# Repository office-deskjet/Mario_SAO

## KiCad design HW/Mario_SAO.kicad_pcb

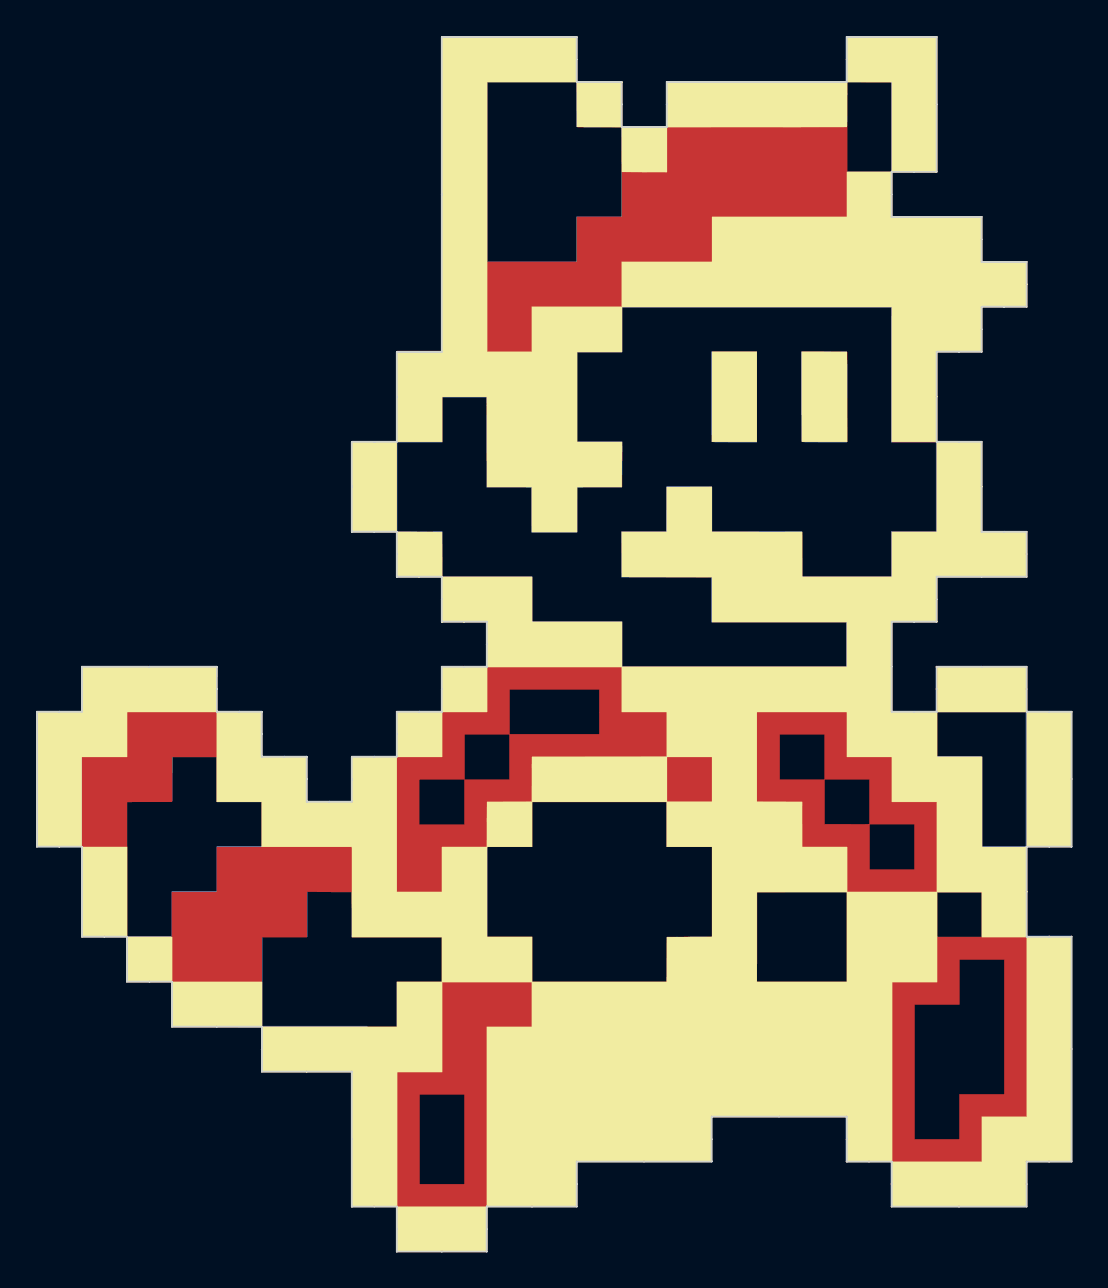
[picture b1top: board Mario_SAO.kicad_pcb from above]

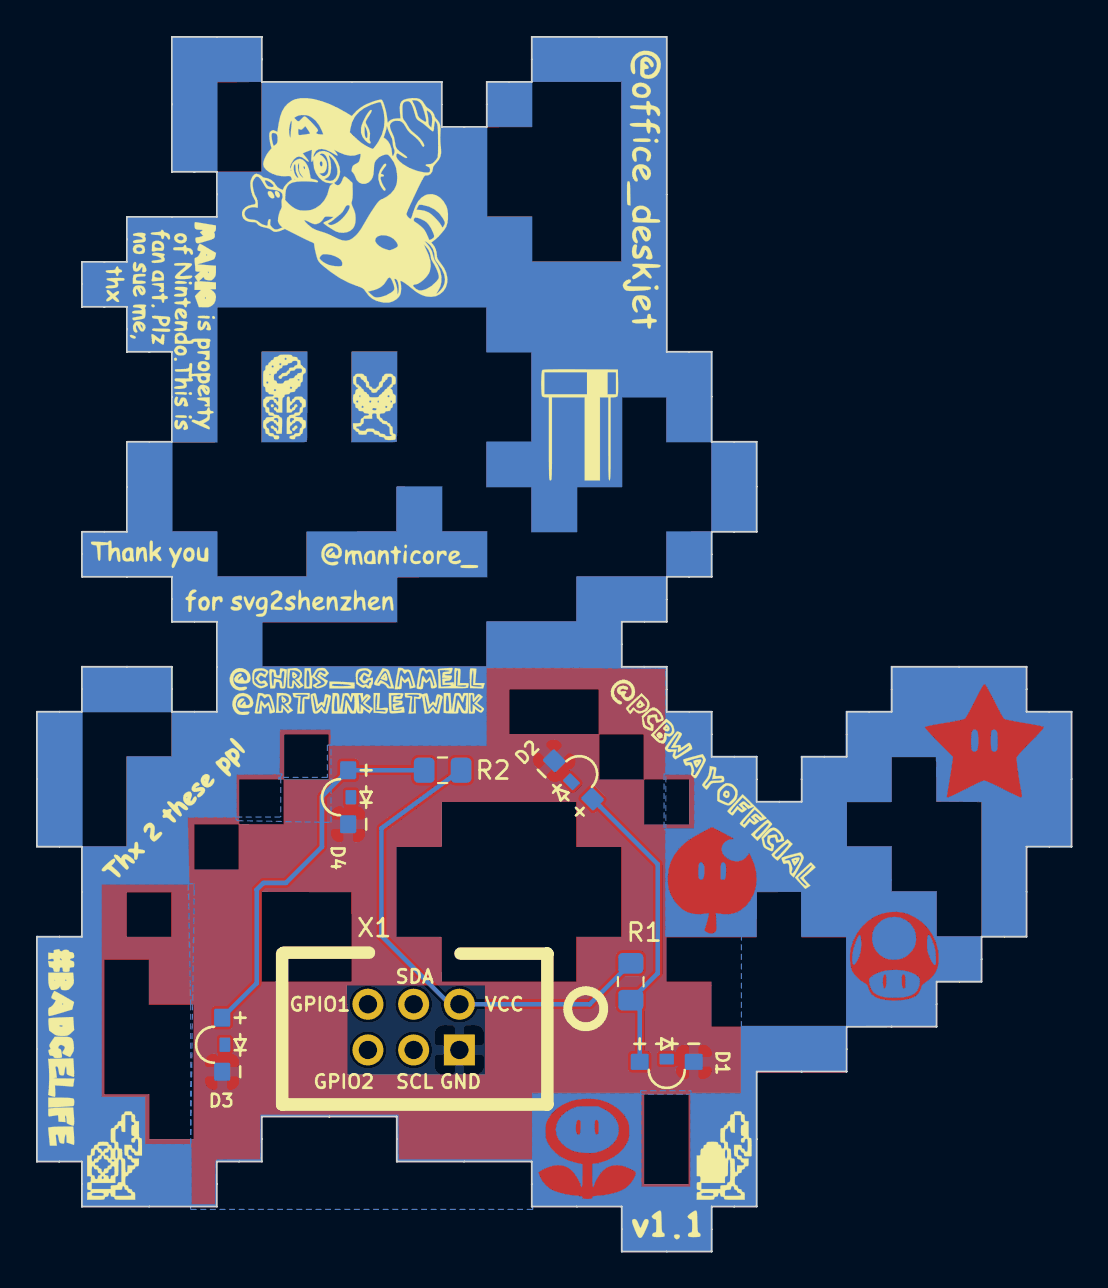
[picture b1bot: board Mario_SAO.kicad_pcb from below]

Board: 2 copper layers, 57.5 x 67.5 mm, 7 parts (6 on the bottom side), 4 nets.

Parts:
D1, D2, D3, D4: LED; 1204_SIDE_VIEW_LED
R1, R2: 50R; R_0805_2012Metric_Pad1.15x1.40mm_HandSolder
X1: Badgelife_sao_connector_v169bis; Badgelife-SAOv169-SAO-2x3

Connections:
GND: D1.1, D2.1, D3.1, D4.1, X1.2
unnamed: D1.2, D2.2, R1.2
unnamed: D3.2, D4.2, R2.2
VCC: R1.1, R2.1, X1.1

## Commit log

2019-05-22 first
2019-05-22 added link to image source
2019-05-22 ignore
2019-06-09 working on getting the layers done
2019-06-09 Art protoype done, working on layout
2019-06-09 added netlist
2019-06-09 fixed footprints in netlist
2019-06-09 Adding netlist and edge.cuts to PCB
2019-06-09 placeing LEDs
2019-06-09 Layer Add footprints
2019-06-09 Adding trace and B.Cu keepout
2019-06-09 added B.Cu keepout
2019-06-09 routed LEDs and ground pour
2019-06-10 Finished F.Cu, Got B.Cu added.
2019-06-10 Adding art
2019-06-10 more B.Cu art
2019-06-10 Added silk art
2019-06-10 more silk
2019-06-10 working on B.Silk
2019-06-12 Finalize B.Silk, sent to fab.
2019-06-19 fixed link to font
2019-06-19 fixed up art and moved an led.
2019-06-28 re-doing B.Cu:
2019-06-30 cleaned up art, final
2019-07-13 Added solder paste jig
2019-07-13 fixed readme
2019-07-13 stl file
